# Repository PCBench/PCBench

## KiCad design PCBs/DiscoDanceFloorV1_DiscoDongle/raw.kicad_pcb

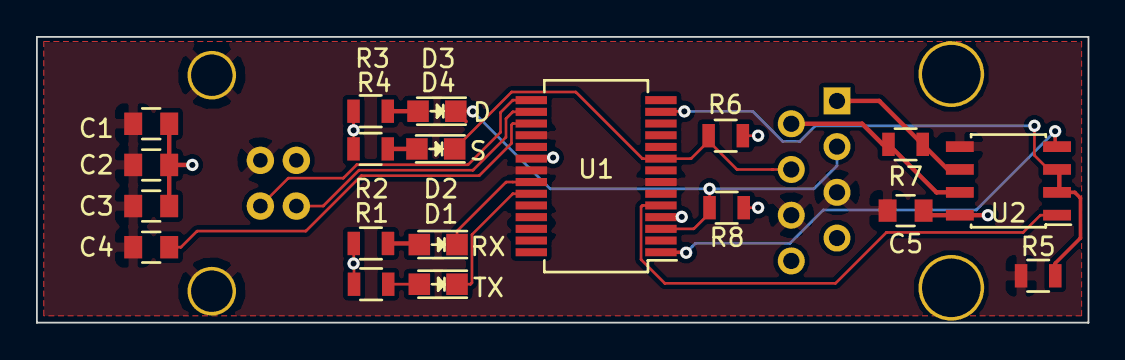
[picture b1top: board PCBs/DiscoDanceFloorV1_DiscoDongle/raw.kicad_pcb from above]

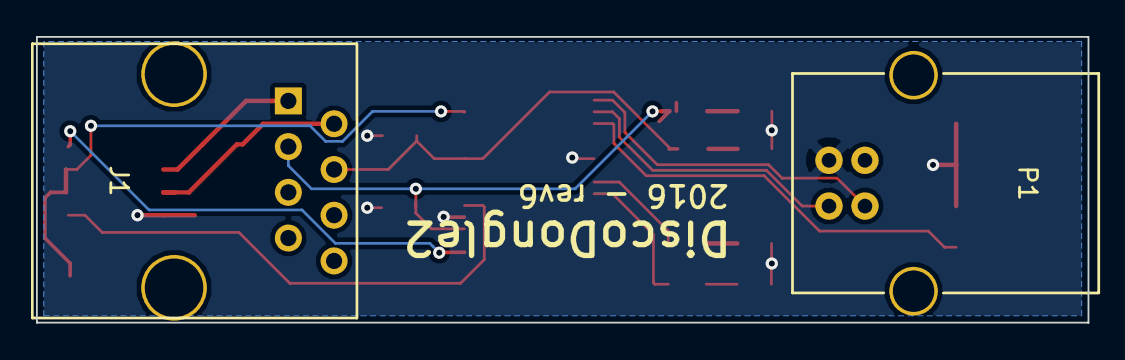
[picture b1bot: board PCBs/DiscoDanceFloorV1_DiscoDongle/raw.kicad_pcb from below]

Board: 2 copper layers, 58.4 x 15.9 mm, 21 parts (2 on the bottom side), 18 nets.

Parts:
C1, C4, C5: 100nF; C_0805
C2: 4.7uF; C_0805
C3: 10nF; C_0805
D1: TX; LED_0805
D2: RX; LED_0805
D3: D; LED_0805
D4: S; LED_0805
J1: RJ45; RJ45_8
P1: USB_B
R1, R2, R3, R4: 200; R_0805
R5, R6, R8: 20k; R_0805
R7: 120; R_0805
U1: FT232RL; SSOP-28_5.3x10.2mm_Pitch0.65mm
U2: ISL81487E; SOIC-8_3.9x4.9mm_Pitch1.27mm

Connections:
+5V: C1.1, C2.1, C3.1, C5.1, P1.1, R1.1, R2.1, R3.1, R4.1, R6.1, R8.1, U1.4, U1.20, U2.8
Daisy: D3.1, J1.3, R8.2, U1.3
GND: C1.2, C2.2, C3.2, C4.2, C5.2, J1.5, J1.6, P1.4, P1.5, R5.2, U1.7, U1.18, U1.21, U1.25, U1.26, U2.5
unnamed: C4.1, U1.17
unnamed: D1.2, R1.2
unnamed: D2.2, R2.2
unnamed: D3.2, R3.2
unnamed: D4.2, R4.2
unnamed: J1.1, R7.2, U2.6
unnamed: J1.2, R7.1, U2.7
unnamed: P1.2, U1.16
unnamed: P1.3, U1.15
unnamed: R5.1, U1.13, U2.2, U2.3
unnamed: U1.1, U2.4
unnamed: U1.5, U2.1
RXLED: D2.1, U1.22
Signal: D4.1, J1.4, R6.2, U1.9
TXLED: D1.1, U1.23

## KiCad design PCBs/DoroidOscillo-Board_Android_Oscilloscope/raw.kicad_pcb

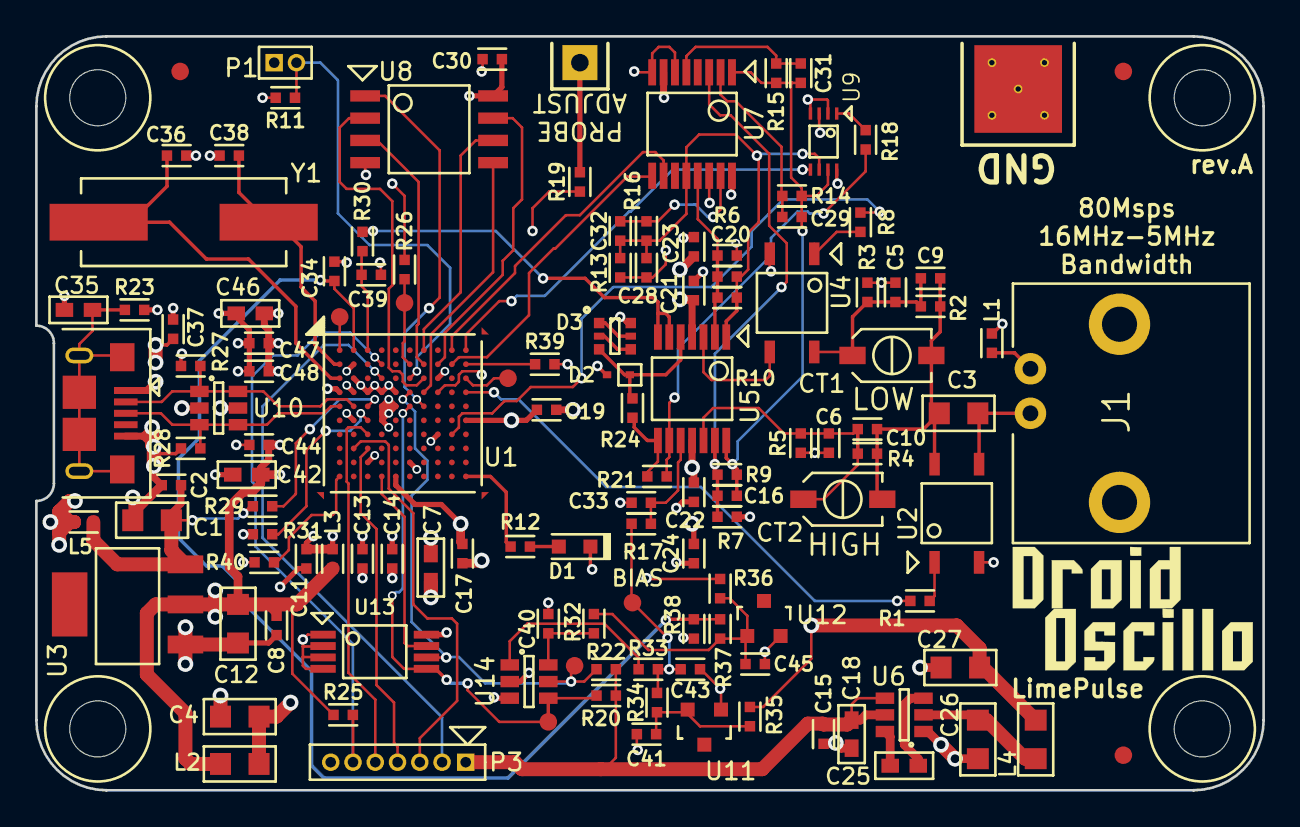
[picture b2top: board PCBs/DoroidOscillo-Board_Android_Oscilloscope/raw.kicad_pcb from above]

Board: 4 copper layers, 70.0 x 43.0 mm, 132 parts (0 on the bottom side), 77 nets.

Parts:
C1, C4, C12, C26, C27: 22u 6.3V; SMD2012
C2, C8, C11, C14, C15, C17, C19, C23, C24, C30, C33, C37, C41, C43, C44, C45, C47: 0.1u; SMD1005
C3: 47n 100V; SMD2012
C5, C32: 4.7p; SMD1005
C6: 120p; SMD1005
C7, C18, C42, C46: 10u 6.3V; SMD1608
C9, C10, C39: NM; SMD1005
C13, C48: 22n; SMD1005
C16, C20: 2.2p; SMD1005
C21, C22, C34, C40: 1u; SMD1005
C25: 4.7u 6.3V; SMD1608
C28: 15p; SMD1005
C29: 3.3p; SMD1005
C31: 10p; SMD1005
C35: 4.7n 100V; SMD1608
C36, C38: 18p; SMD1005
CT1: TZC3R100A110 3p-10p; MURATA_TZC3
CT2: TZC3Z030A110R00 1.4p-3p; MURATA_TZC3
D1: APT1608EC; SMD1608_DIODE
D2: RB521S30T5G; SOD-523
D3: BAS16VY; SOT-363
FID1: Fiducial_C; Fiducial_1mm
FID2: Fiducial_A; Fiducial_1mm
FID3: Fiducial_B; Fiducial_1mm
HOLE3MM_NC, HOLE3MM_NC#2, HOLE3MM_NC#3, HOLE3MM_NC#4: VAL**; HOLE3MM_NC
J1: BNC; BNC-R
L1, L5: BLM15AG121SN1; SMD1005
L2, L4: LBR2012T202K; SMD2012
L3: BLM15AG601SN1; SMD1005
P1: USB_BOOT; PIN_HEADER_2_1.27mm
P2: FCI_10118193-0001LF; 10118193-0001LF
P3: JTAG; PIN_HEADER_7_1.27pitch
R1, R8, R11, R36, R39, R40: 2.2k 5%; SMD1005
R2: 1100k 1%; SMD1005
R3: 910k 1%; SMD1005
R4: 1.96M 1%; SMD1005
R5: 36k 1%; SMD1005
R6, R7: 3k 1%; SMD1005
R9, R10: 27k 1%; SMD1005
R12: 10k 5%; SMD1005
R13: 3.3k 1%; SMD1005
R14: 22k 1%; SMD1005
R15: 5.6k 1%; SMD1005
R16: 13.3k 1%; SMD1005
R17, R32: 4.7k 5%; SMD1005
R18: 910 1%; SMD1005
R19, R29: 100 5%; SMD1005
R20, R22, R25, R26: 4.7k; SMD1005
R21: 1k 1%; SMD1005
R23, R27, R28: 1M 5%; SMD1005
R24: 680 1%; SMD1005
R30: 0; SMD1005
R31: 12k 1%; SMD1005
R33: 2k 1%; SMD1005
R34: 8.2k 1%; SMD1005
R35, R38: 1.5k 1%; SMD1005
R37: 2.2k 1%; SMD1005
TP1: SCL; TestPad
TP2: SDA; TestPad
TP3: RST; TestPad
U1: LPC4370FET100; TFBGA100_MYREFLOW
U2, U4: CPC1017N
U3: AMS1117-3.3; SOT-223
U5: OPA4354AIPWR; TSSOP-14_4.4x5mm_Pitch0.65mm
U6: LM2664; SOT-23-6
U7: 74HC4052PW; TSSOP-16_4.4x5mm_Pitch0.65mm
U8: W25Q80BVSSIG; SOIJ-8_5.3x5.3mm_Pitch1.27mm
U9: TC7W53FK; SSOP8_P0.5W2.3
U10: USBLC6-2SC6; SOT-23-6
U11, U12: LM385M3-1.2/NOPB; SOT-23
U13: AT24C02C-XHM-T; TSSOP-8_4.4x3mm_Pitch0.65mm
U14: MCP4726A0T-E/CH; SOT-23-6
W1: ISP; TestPad
W2: PROBE_COMP_HOLE
W3: ADC1; TestPad
W4: PROBE_GND_PAD; Probe-ADJ-GND
W5: TP_BIAS; TestPad
Y1: ABLS-12.000MHZ-B4-T; Crystal_HC49-SD_SMD

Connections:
/USB_D+: P2.3, R28.1, U1.E1, U10.3, U10.4
/USB_D-: P2.2, R27.1, U1.E2, U10.1, U10.6
/USB_VBUS: R29.1, U1.E3
ADCHS_VNEG: C39.1, R30.2, U1.A3
ADCHS_VPOS0: C34.1, R37.2, R38.1, U1.A2
BIAS: C43.2, R17.1, R33.2, R34.1, W5.1
BOOT1: R40.1, U1.K1
BOOT2: P1.2, R11.1, U1.C6
BOOT3: R39.1, U1.B10
BOOT_ISP: U1.C10, W1.1
DAC_OUT: R33.1, U14.1
DAC_VREF: C45.1, R32.1, R36.2, R37.1, U12.1
DC_SW: R1.1, U1.D10
EEPROM_WP: U1.K4, U13.7
GND: C1.2, C2.2, C4.2, C5.2, C6.2, C7.2, C8.2, C11.2, C12.2, C13.2, C14.2, C15.2, C17.2, C18.2, C19.2, C21.2, C22.1, C23.2, C24.1, C26.2, C27.2, C30.2, C33.2, C34.2, C35.2, C36.1, C37.2, C38.1, C39.2, C40.1, C41.2, C42.2, C43.1, C44.2, C45.2, C46.2, C47.2, C48.2, D1.1, D2.2, D3.6, L1.2, P2.5, P3.7, R3.1, R5.2, R6.2, R7.2, R11.2, R23.2, R27.2, R28.2, R31.2, R38.2, R39.2, R40.2, U1.C2, U1.C8, U1.D3, U1.D4, U1.D5, U1.F2, U1.G8, U1.J3, U1.J6, U2.2, U3.1, U4.2, U6.1, U7.6, U7.8, U8.4, U9.2, U9.4, U10.2, U11.1, U12.2, U13.1, U13.2, U13.3, U13.4, U14.2, W4.1
I2C_SCL: R22.2, TP1.1, U1.D6, U13.6, U14.5
I2C_SDA: R20.2, TP2.1, U1.E6, U13.5, U14.4
JTAG_RESET: P3.6, R25.2, U1.B4
JTAG_TCK: P3.3, U1.H2
JTAG_TDI: P3.5, U1.G3
JTAG_TDO: P3.4, U1.H3
JTAG_TMS: P3.2, U1.C4
LED0: R12.1, U1.K10
MUX0-S0: U1.A9, U7.10
MUX0-S1: U1.B9, U7.9
MUX1-A: U1.A10, U9.5
unnamed: C3.1, J1.C, U2.3
unnamed: C5.1, C9.2, CT1.2, R2.1, R3.2, U4.4
unnamed: C3.2, C9.1, C10.1, CT1.1, CT2.1, R2.2, R4.1, U2.4
unnamed: C6.1, C10.2, CT2.2, R4.2, R5.1, U5.12
unnamed: C7.1, C11.1, C13.1, C14.1, L3.2, U1.E4, U1.E5, U1.F4
unnamed: C16.1, C29.2, C31.2, R9.2, R14.2, R15.2, U5.14, U7.1, U9.7
unnamed: C16.2, R7.1, R9.1, U5.13, U7.3
unnamed: C20.1, R6.1, R10.2, U5.2, U7.13
unnamed: C20.2, C28.1, C32.1, R10.1, R13.1, R16.1, U5.1, U7.12, U9.6
unnamed: C25.1, U6.6
unnamed: C25.2, U6.3
unnamed: C26.1, L4.1, U6.2
unnamed: C28.2, R13.2, U7.14
unnamed: C29.1, R14.1, U7.2
unnamed: C31.1, R15.1, U7.5
unnamed: C32.2, R16.2, U7.15
unnamed: C33.1, R17.2, U5.10
unnamed: C35.1, P2.S1, P2.S2, P2.S3, P2.S4, P2.S5, P2.S6, R23.1
unnamed: C36.2, U1.C1, Y1.1
unnamed: C37.1, L5.1, P2.1, U10.5
unnamed: C38.2, U1.B1, Y1.2
unnamed: C40.2, R32.2, U14.6
unnamed: C41.1, R34.2, R35.1, U11.2
unnamed: D1.2, R12.2
unnamed: D2.1, D3.3, R24.2, U5.5
unnamed: D3.1, D3.5
unnamed: D3.2, D3.4
unnamed: J1.S, L1.1
unnamed: R1.2, U2.1
unnamed: R8.1, U4.1
unnamed: R18.1, R21.2, U5.9
unnamed: R18.2, U9.1
unnamed: R19.1, W2.1
unnamed: R21.1, R24.1, U5.8
unnamed: R26.2, TP3.1, U1.B6
unnamed: R30.1, U5.6, U5.7
unnamed: R31.1, U1.F3
unnamed: U1.A1, W3.1
unnamed: U4.3, U5.3
OP_SW: R8.2, U1.G9
PROBE_COMP: R19.2, U1.D8
SPIFI_CS: U1.E7, U8.1
SPIFI_MISO: U1.C7, U8.2
SPIFI_MOSI: U1.D7, U8.5
SPIFI_SCK: U1.A7, U8.6
SPIFI_SIO2: U1.B7, U8.3
SPIFI_SIO3: U1.B8, U8.7
VBUS: C1.1, C2.1, L5.2, R29.2, U3.3
alt_3.3VD: C8.1, C12.1, C15.1, C17.1, C18.1, C19.1, C30.1, C42.1, C44.1, C46.1, C47.1, C48.1, L2.1, L3.1, P1.1, P3.1, R20.1, R22.1, R25.1, R26.1, U1.B2, U1.D1, U1.D2, U1.F10, U1.K5, U3.2, U6.4, U6.5, U8.8, U13.8
alt_VAA+: C4.1, C21.1, C23.1, L2.2, R36.1, U5.4, U7.16, U9.8, U14.3
alt_VAA-: C22.2, C24.2, C27.1, L4.2, R35.2, U5.11, U7.7, U9.3

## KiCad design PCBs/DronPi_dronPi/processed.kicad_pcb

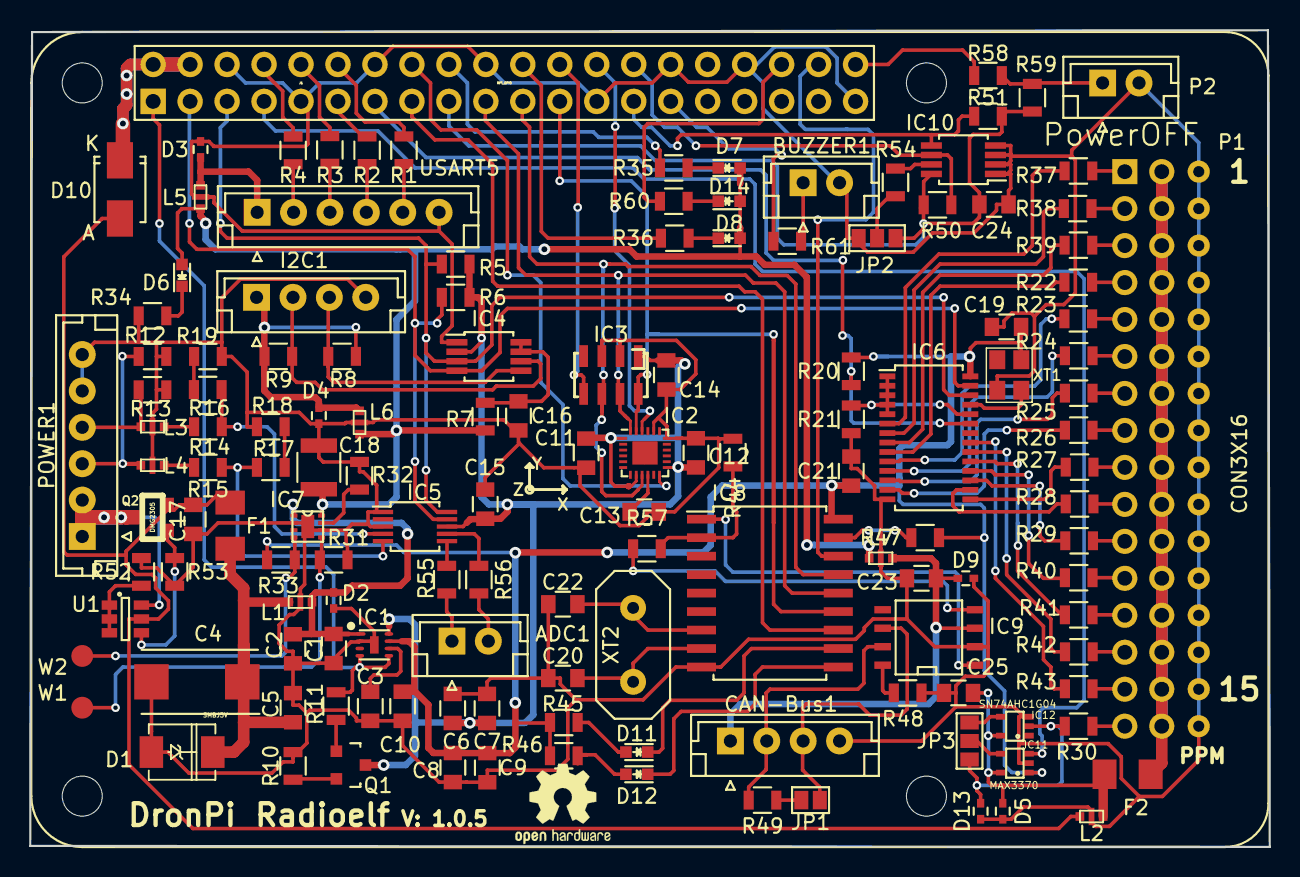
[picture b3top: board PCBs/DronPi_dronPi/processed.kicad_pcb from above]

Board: 2 copper layers, 85.2 x 56.1 mm, 141 parts (0 on the bottom side), 125 nets.

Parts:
ADC1: CONN_01X02; JST_EH_B02B-EH-A_02x2.50mm_Straight
BUZZER1: CONN_01X04; JST_EH_B02B-EH-A_02x2.50mm_Straight
C1, C5, C7, C10, C11, C14, C15, C16, C19, C21, C23, C24, C25: 100nF; C_0805
C2: 10uF; C_0805
C3: 2u2F; C_0805
C4: 220uF; TantalC_SizeD_EIA-7343_Reflow
C6, C9, C17: 22uF; C_0805
C8: 1uF; C_0805
C12: 10nF; C_0805
C13: 2u2; C_0805
C18: 100uF; C_1210
C20, C22: 22pF; C_0805
CAN-Bus1: JST_4PIN; JST_EH_B04B-EH-A_04x2.50mm_Straight
D1: SMBJ5V; DO-214AA
D2, D3, D4, D5, D9, D13: PESD0402-140; C_0402
D6: LED_rojo; LED_0603
D7: LED_verde; LED_0603
D8: LED_azul; LED_0603
D10: STPS1L30A; SMA_Standard
D11: verde; LED_0603
D12: Rojo; LED_0603
D14: LED_blanco; LED_0603
F1, F2: 0ZCA0035FF2G; Fuse_SMD1206_Wave
I2C1: JST_4PIN; JST_EH_B04B-EH-A_04x2.50mm_Straight
IC1: MIC5332; MLF-8-1EP
IC2: MPU-9250; QFN-24-1EP_3x3mm_Pitch0.4mm
IC3: MS5611-01BA; MS5611
IC4: PCA9306; MSOP-8_3x3mm_Pitch0.65mm
IC5: ADC_ADS1115; MSOP-10_3x3mm_Pitch0.5mm
IC6: PCA9685; TSSOP-28_4.4x9.7mm_Pitch0.65mm
IC7: BQ24315; BQ24313_DSG_8
IC8: MCP2515; SOIC-18
IC9: MCP2551; SOIC-8-N
IC10: 24AA32; MSOP-8_3x3mm_Pitch0.65mm
IC11: MAX3370; SC70-5
IC12: SN74AHC1G04; SC70-5
J1: RPi_GPIO; raspberrypi2
JP1: JUMPER; GS2
JP2, JP3: JUMPER3; GS3
L1, L2, L3, L4, L5, L6, L7: KNH16C104DA5TS; KYOCERA-KNH16-DA
M1: OSHW-LOGOS; OSHW-Logo2_7.3x6mm_SilkScreen
P1: CONN_3X16; IDC_Header_Straight_34pins
P2: PowerOff; JST_EH_B02B-EH-A_02x2.50mm_Straight
POWER1: JST_6PIN; JST_EH_B06B-EH-A_06x2.50mm_Straight
Q1: MMBT3906LT1; SOT-23
Q2: DMG2305; SOT23-3
R1, R2, R3, R4, R49: 120R; R_0805
R5, R6, R8, R9: 1K5; R_0805
R7: 200K; R_0805
R10: 10R; R_0805
R11: 1k8; R_0805
R12, R13, R33: 1M; R_0805
R14, R15, R16, R17, R18, R19, R55, R56: 10K/0.1%; R_0805
R20, R21, R31, R47: 10K; R_0805
R22, R23, R24, R25, R26, R27, R28, R29, R37, R38, R39, R40, R41, R42, R43: 220; R_0805
R30: 100; R_0805
R32: 24K; R_0805
R34, R35, R60: 680; R_0805
R36: 820; R_0805
R44: 18K; R_0805
R45, R46: 560; R_0805
R48, R54: 1K; R_0805
R50: 3K9; R_0805
R51: 3k9; R_0805
R52: 47k; R_0805
R53: 47K; R_0805
R57, R59: 10k; R_0805
R58: 1k; R_0805
R61: 100R; R_0805
U1: DMMT5401; SOT-23-6
USART5: JST_6PIN; JST_EH_B06B-EH-A_06x2.50mm_Straight
W1: REG_CE; Measurement_Point_Round-SMD-Pad_Small
W2: REG_FAULT; Measurement_Point_Round-SMD-Pad_Small
XT1: CRYSTAL_ASE-25mhz; ASEseries
XT2: 16Mhz; HC-18UV

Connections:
3v3: C24.2, IC10.8, J1.17, JP2.1, R50.1, R51.1, R59.1
3v3_EN: IC1.4, IC1.5, J1.1, R11.1
+3v3: C6.1, C7.1, C11.1, C12.1, C14.1, C15.1, IC1.8, IC2.1, IC2.8, IC2.13, IC3.1, IC4.2, IC5.8, Q1.3, R5.1, R6.1
+5v_SERV: C25.2, D5.1, F2.2, IC11.5, IC12.5, L2.P$2
/I2C/SCL2: I2C1.2, IC4.6, R9.2
/I2C/SDA2: I2C1.3, IC4.5, R8.2
/PWM-PPM-SBUS/PPM_: D13.1, IC12.2, JP3.1, R30.2
/PWM-PPM-SBUS/SBUS_: IC12.4, JP3.3
/Proteccion/REG_CE: IC7.5, R31.2, W1.1
/Proteccion/REG_FAULT: IC7.4, R33.1, W2.1
ANL_I: L4.P$1, POWER1.3, R12.1
ANL_V: L3.P$1, POWER1.4, R13.1
BBB_+3v3: C8.1, C9.1, C10.1, C19.1, C21.2, IC1.7, IC6.28, IC8.18, IC11.1, R20.1, R33.2, R45.1, R46.1, R47.2, XT1.4
BUZZER: J1.29, R61.2
GND: BUZZER1.2, C1.2, C2.2, C3.2, C4.2, C5.2, C6.2, C7.2, C8.2, C9.2, C10.2, C11.2, C12.2, C13.2, C14.2, C15.2, C16.2, C17.2, C18.2, C19.2, C20.2, C21.1, C22.2, C23.2, C24.1, C25.1, CAN-Bus1.4, D1.1, D2.2, D3.2, D4.2, D5.2, D9.2, D13.2, I2C1.4, IC1.2, IC1.9, IC2.18, IC2.20, IC3.2, IC3.3, IC4.1, IC5.1, IC5.3, IC6.14, IC7.2, IC7.6, IC7.9, IC8.9, IC9.2, IC10.1, IC10.2, IC10.3, IC10.4, IC11.2, IC12.3, J1.6, J1.9, J1.14, J1.20, J1.25, J1.30, J1.34, J1.39, JP2.3, L1.P$3, L1.P$4, L1.P$5, L2.P$3, L2.P$4, L2.P$5, L3.P$3, L3.P$4, L3.P$5, L4.P$3, L4.P$4, L4.P$5, L5.P$3, L5.P$4, L5.P$5, L6.P$3, L6.P$4, L6.P$5, L7.P$3, L7.P$4, L7.P$5, P1.3, P1.6, P1.9, P1.12, P1.15, P1.18, P1.21, P1.24, P1.27, P1.30, P1.33, P1.36, P1.39, P1.42, P1.45, P1.48, P2.2, POWER1.5, POWER1.6, R10.2, R12.2, R13.2, R18.2, R19.2, R21.2, R31.1, R32.1, R34.2, R44.1, R48.2, R52.2, R53.2, USART5.6, XT1.2
HAT_SCL: IC10.6, J1.28, R50.2
HAT_SDA: IC10.5, J1.27, R51.2
INT_CAN: IC8.12, J1.15
LED_1: J1.18, R35.2
LED_2: J1.22, R36.2
LED_3: J1.36, R60.2
MPU_INT: IC2.12, J1.16
unnamed: ADC1.1, R55.2
unnamed: ADC1.2, R56.2
unnamed: BUZZER1.1, R61.1
unnamed: C3.1, IC1.6
unnamed: C4.1, C5.1, D1.2, F1.2, L1.P$1
unnamed: C13.1, IC2.10
unnamed: C16.1, IC4.7, IC4.8, R7.2
unnamed: C20.1, IC8.8, XT2.1
unnamed: C22.1, IC8.7, XT2.2
unnamed: C23.1, CAN-Bus1.1, D9.1, IC9.3, L7.P$2
unnamed: CAN-Bus1.2, IC9.7, R49.2
unnamed: CAN-Bus1.3, IC9.6, JP1.2
unnamed: D3.1, L5.P$1, USART5.1
unnamed: D4.1, I2C1.1, L6.P$2, R8.1, R9.1
unnamed: D6.1, R34.1
unnamed: D7.1, R35.1
unnamed: D8.1, R36.1
unnamed: D11.1, IC8.11
unnamed: D11.2, R45.2
unnamed: D12.1, IC8.10
unnamed: D12.2, R46.2
unnamed: D14.1, R60.1
unnamed: F2.1, P1.2, P1.5, P1.8, P1.11, P1.14, P1.17, P1.20, P1.23, P1.26, P1.29, P1.32, P1.35, P1.38, P1.41, P1.44, P1.47
unnamed: IC5.4, R14.2, R16.2
unnamed: IC5.5, R15.1, R17.2
unnamed: IC5.6, R55.1
unnamed: IC5.7, R56.1
unnamed: IC6.1, IC6.2, IC6.3, IC6.4, IC6.5, IC6.24, R21.1
unnamed: IC6.6, R37.2
unnamed: IC6.7, R38.2
unnamed: IC6.8, R39.2
unnamed: IC6.9, R22.2
unnamed: IC6.10, R23.2
unnamed: IC6.11, R24.2
unnamed: IC6.12, R25.2
unnamed: IC6.13, R26.2
unnamed: IC6.15, R27.2
unnamed: IC6.16, R28.2
unnamed: IC6.17, R29.2
unnamed: IC6.18, R40.2
unnamed: IC6.19, R41.2
unnamed: IC6.20, R42.2
unnamed: IC6.21, R43.2
unnamed: IC6.25, XT1.3
unnamed: IC7.7, R32.2
unnamed: IC8.1, IC9.1
unnamed: IC8.2, R44.2, R57.2
unnamed: IC8.17, R47.1
unnamed: IC9.4, R57.1
unnamed: IC9.8, R48.1
unnamed: IC10.7, R54.2
unnamed: IC11.4, JP3.2
unnamed: JP1.1, R49.1
unnamed: JP2.2, R54.1
unnamed: L3.P$2, R14.1
unnamed: L4.P$2, R15.2
unnamed: P1.1, R37.1
unnamed: P1.4, R38.1
unnamed: P1.7, R39.1
unnamed: P1.10, R22.1
unnamed: P1.13, R23.1
unnamed: P1.16, R24.1
unnamed: P1.19, R25.1
unnamed: P1.22, R26.1
unnamed: P1.25, R27.1
unnamed: P1.28, R28.1
unnamed: P1.31, R29.1
unnamed: P1.34, R40.1
unnamed: P1.37, R41.1
unnamed: P1.40, R42.1
unnamed: P1.43, R43.1
unnamed: P1.46, R30.1
unnamed: P2.1, R58.1, R59.2
unnamed: POWER1.1, POWER1.2, Q2.3, U1.6
unnamed: Q1.1, R11.2
unnamed: Q1.2, R10.1
unnamed: Q2.1, R53.1, U1.4
unnamed: R1.2, USART5.5
unnamed: R2.2, USART5.4
unnamed: R3.2, USART5.3
unnamed: R4.2, USART5.2
unnamed: R16.1, R19.1
unnamed: R17.1, R18.1
unnamed: R52.1, U1.1, U1.2, U1.3
PPM: IC11.3, J1.7
PWM_EN: IC6.23, J1.13, R20.2
Power: C17.1, D10.2, F1.1, L2.P$1, Q2.2, U1.5
PowerOff: J1.40, R58.2
SCL: IC4.3, IC5.10, IC6.26, J1.5, R5.2
SDA: IC4.4, IC5.9, IC6.27, J1.3, R6.2
SPI_CLK: IC2.23, IC3.8, IC8.13, J1.23
SPI_CS_BARO: IC3.5, J1.24
SPI_CS_CAN: IC8.16, J1.38
SPI_CS_MPU: IC2.22, J1.26
SPI_MISO: IC2.9, IC3.6, IC8.15, J1.21
SPI_MOSI: IC2.24, IC3.7, IC8.14, J1.19
UART_CTS: J1.11, R2.1
UART_RTS: J1.12, R1.1
UART_RX: J1.10, R3.1
UART_TX: J1.8, R4.1
VCC_AUX: C18.1, D6.2, D7.2, D8.2, D14.2, IC7.8, L5.P$2, L6.P$1, L7.P$1, R7.1
VDD: D10.1, J1.2, J1.4
VDD_5v: C1.1, C2.1, D2.1, IC1.1, IC7.1, L1.P$2

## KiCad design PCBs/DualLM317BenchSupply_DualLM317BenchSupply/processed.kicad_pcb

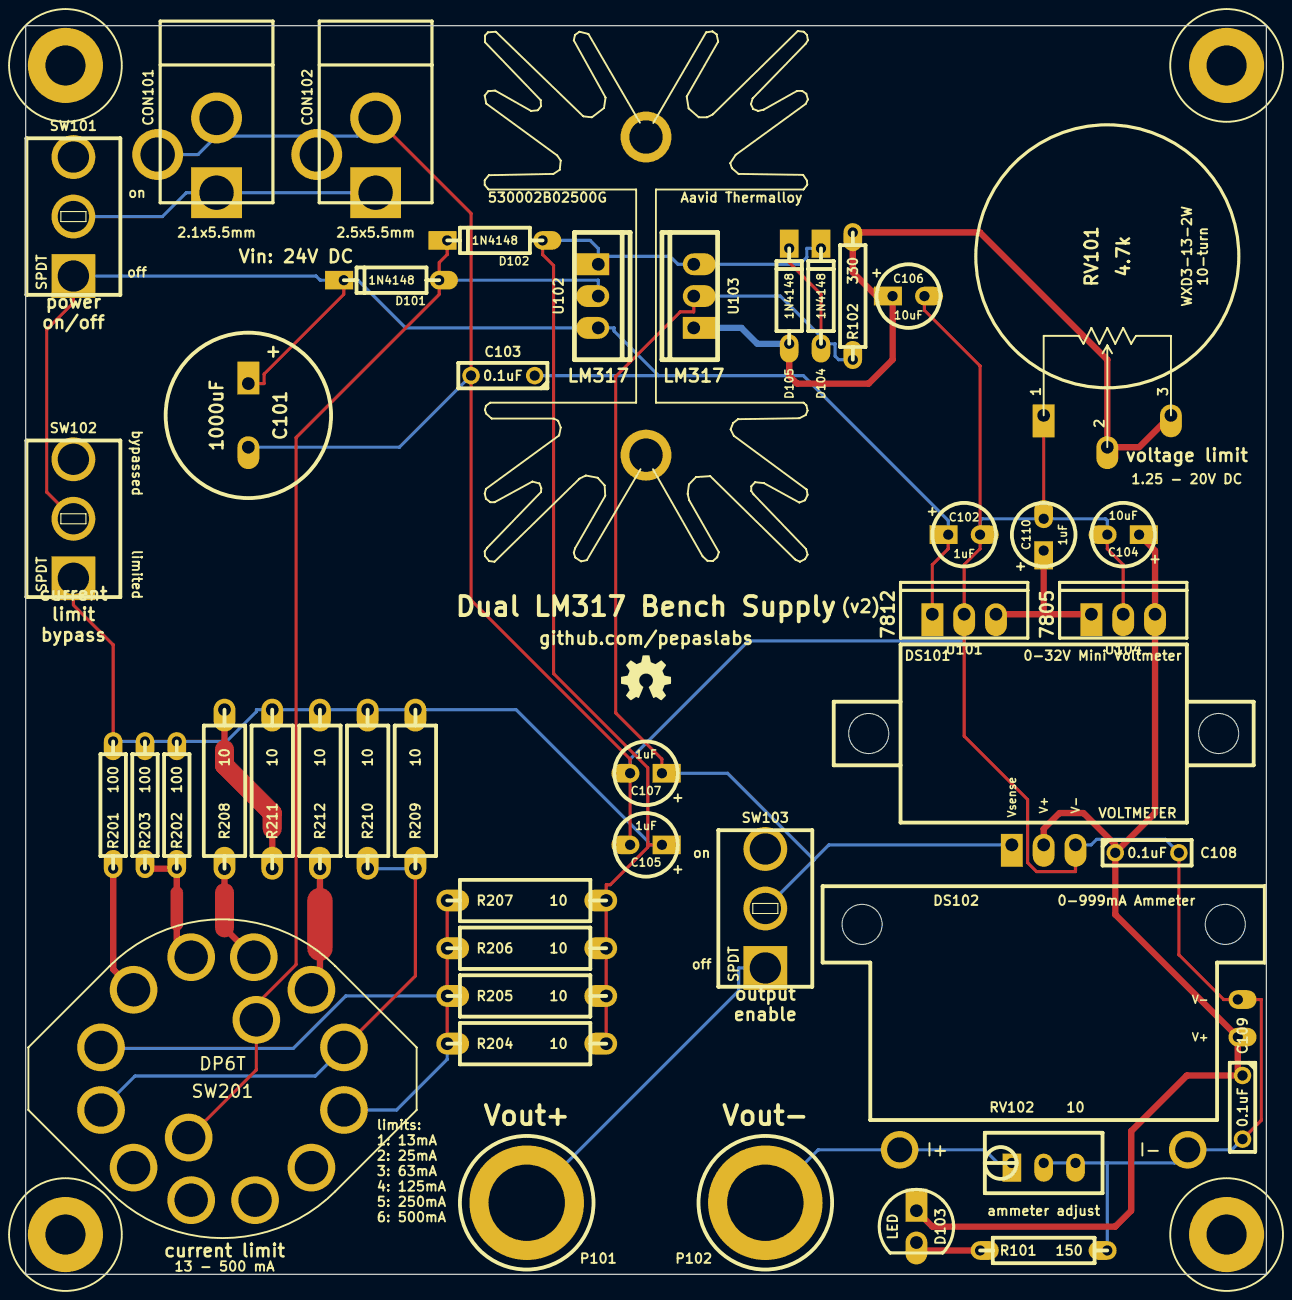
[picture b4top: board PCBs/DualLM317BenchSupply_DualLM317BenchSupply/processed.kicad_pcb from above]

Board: 2 copper layers, 99.1 x 99.7 mm, 50 parts (0 on the bottom side), 19 nets.

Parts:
C101: 1000uF; ELCAP_20_52_V
C102, C105, C107, C110: 1uF; ELCAP_10_20_V
C103, C108, C109: 0.1uF; C2
C104, C106: 10uF; ELCAP_10_20_V
CON101: BARREL_JACK; BARREL_JACK_21x55
CON102: BARREL_JACK; BARREL_JACK_25x55
D101, D102, D104, D105: 1N4148; DIODE_3
D103: LED; LED_5MM
DS101: VOLTMETER; DVM036A
DS102: AMMETER_V; EBAY_AMMETER
H101, H102, H103, H104: HOLE; hole_M3
H***: 530002B02500G
P101: Vout+; Banana_A
P102: Vout-; Banana_A
R101: 150; R_AXIAL_0W25
R102: 330; R_AXIAL_0W25
R201, R202, R203: 100; R_AXIAL_0W25
R204, R205, R206, R207, R208, R209, R210, R211, R212: 10; R_AXIAL_0W5
RV101: 4.7k; WXD3-13-2W_A
RV102: 10; 3296W
SW101, SW102, SW103: SPDT; M2012SS1W01
SW201: DP6T; G3SR022-R
U101: 7812; TO-220_V_069B
U102, U103: LM317; TO-220_V_069B
U104: 7805; TO-220_V_069B

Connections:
5V: C104.1, C108.1, C109.1, D103.1, DS101.2, DS102.3, U104.3
12V: C110.1, U101.3, U104.1
/current_limit_r/R_LIM+: D101.1, D102.2, SW201.1, SW201.8, U102.2
/current_limit_r/R_LIM-: C105.1, D102.1, D104.2, R201.2, R202.2, R203.2, R204.2, R205.2, R206.2, R207.2, R209.2, R210.2, R211.2, R212.2, SW102.1, U102.1, U103.3
GND: C101.2, C102.2, C103.2, C104.2, C105.2, C106.2, C107.2, C108.2, C109.2, C110.2, CON101.2, CON101.3, CON102.2, CON102.3, DS101.3, DS102.2, DS102.4, R101.2, RV101.1, RV102.2, RV102.3, U101.2, U104.2
unnamed: C107.1, D104.1, D105.2, DS101.1, R102.1, SW103.2, U103.2
unnamed: C106.1, D105.1, R102.2, RV101.2, RV101.3, U103.1
unnamed: P101.1, SW103.1
unnamed: DS102.1, P102.1, RV102.1
unnamed: D103.2, R101.1
unnamed: CON101.1, CON102.1, SW101.2
unnamed: C101.1, C102.1, C103.1, D101.2, SW101.1, SW102.2, U101.1, U102.3
unnamed: R209.1, R210.1, SW201.6, SW201.13
unnamed: R204.1, R205.1, R206.1, R207.1, SW201.7, SW201.14
unnamed: R208.2, R211.1
unnamed: R212.1, SW201.5
unnamed: R208.1, SW201.4
unnamed: R201.1, SW201.2
unnamed: R202.1, R203.1, SW201.3

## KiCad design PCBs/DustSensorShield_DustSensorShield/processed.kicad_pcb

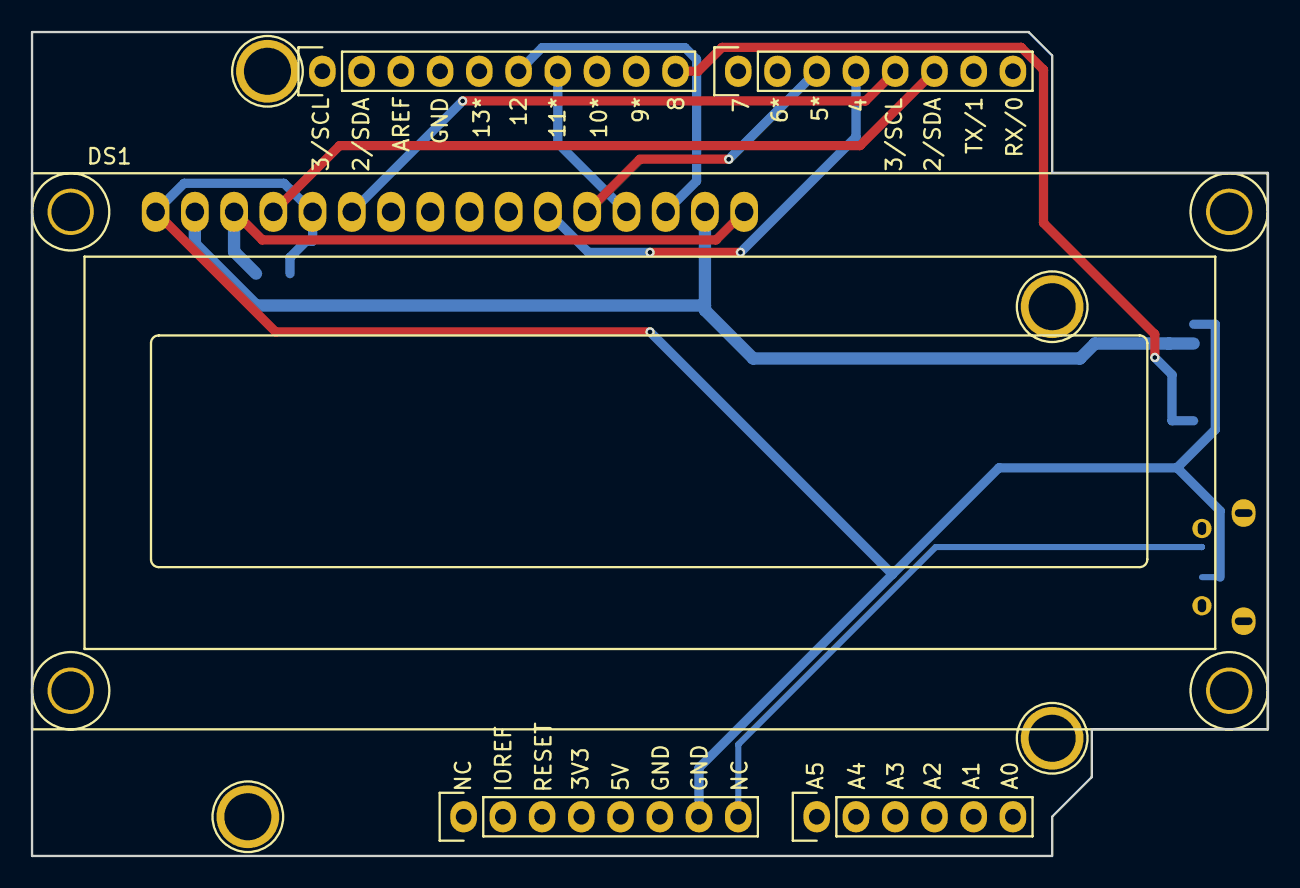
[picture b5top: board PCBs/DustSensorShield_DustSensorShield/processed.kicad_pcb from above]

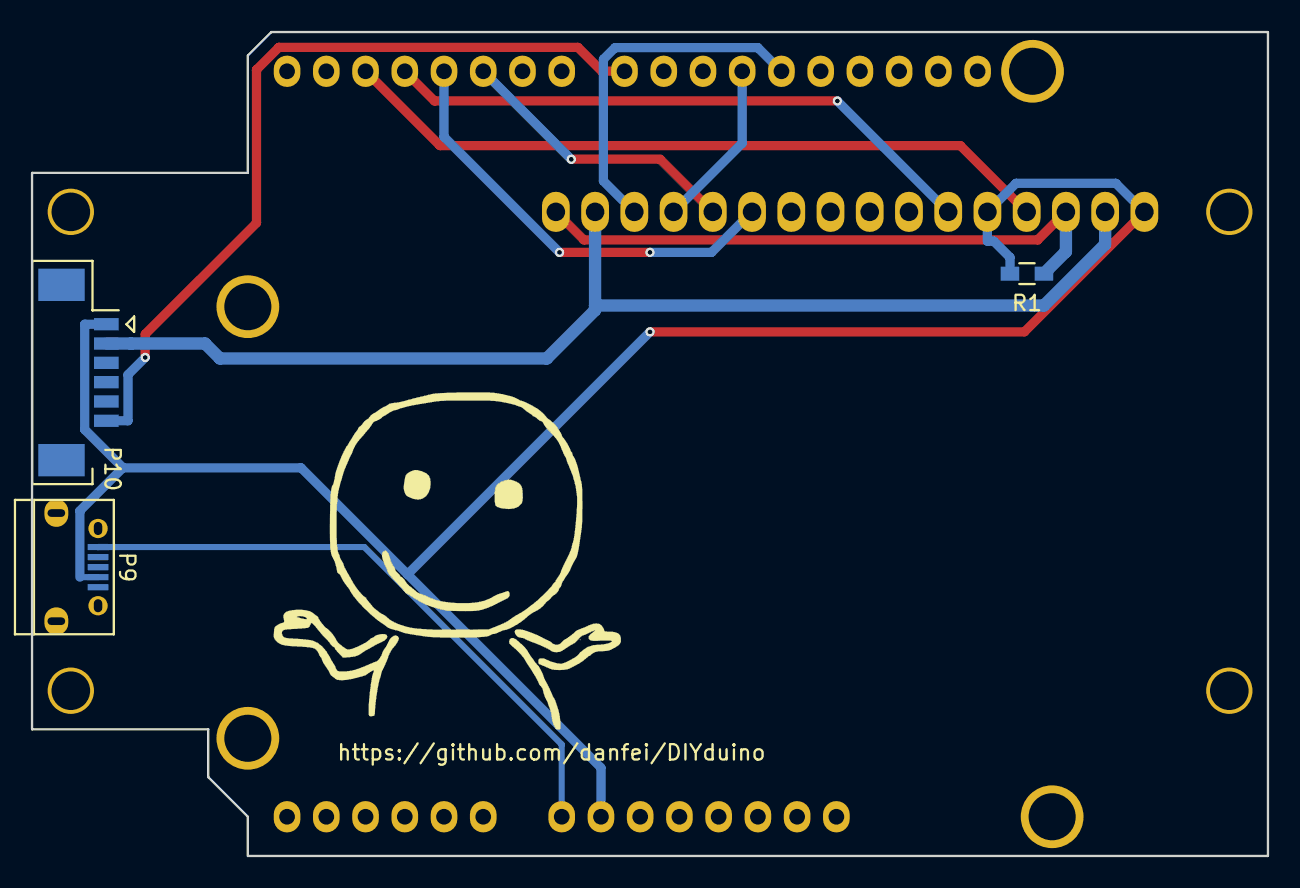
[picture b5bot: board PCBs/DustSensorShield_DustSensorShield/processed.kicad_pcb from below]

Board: 2 copper layers, 80.0 x 53.3 mm, 12 parts (3 on the bottom side), 11 nets.

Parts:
DS1: LCD16X2; WC1602A
P1: Power; Socket_Strip_Arduino_1x08
P2: Analog; Socket_Strip_Arduino_1x06
P3: Digital; Socket_Strip_Arduino_1x10
P4: Digital; Socket_Strip_Arduino_1x08
P5, P6, P7, P8: CONN_1; Arduino_1pin
P9: USB_B; USB_Micro-B
P10: CONN_01X06; Molex_PicoBlade_53261-0671
R1: 91R; R_0603_HandSoldering

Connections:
+5V: DS1.2, DS1.15, P10.2
/IO2: DS1.4, P4.6
/IO3: DS1.6, P4.5
/IO4: DS1.11, P4.4
/IO5: DS1.12, P4.3
/IO8: P3.10, P10.6
/IO11: DS1.13, P3.7
/IO12: DS1.14, P3.6
/VIN: P1.8, P9.1
GND: DS1.1, DS1.5, P1.7, P9.4, P10.1, R1.2
unnamed: DS1.3, DS1.16, R1.1

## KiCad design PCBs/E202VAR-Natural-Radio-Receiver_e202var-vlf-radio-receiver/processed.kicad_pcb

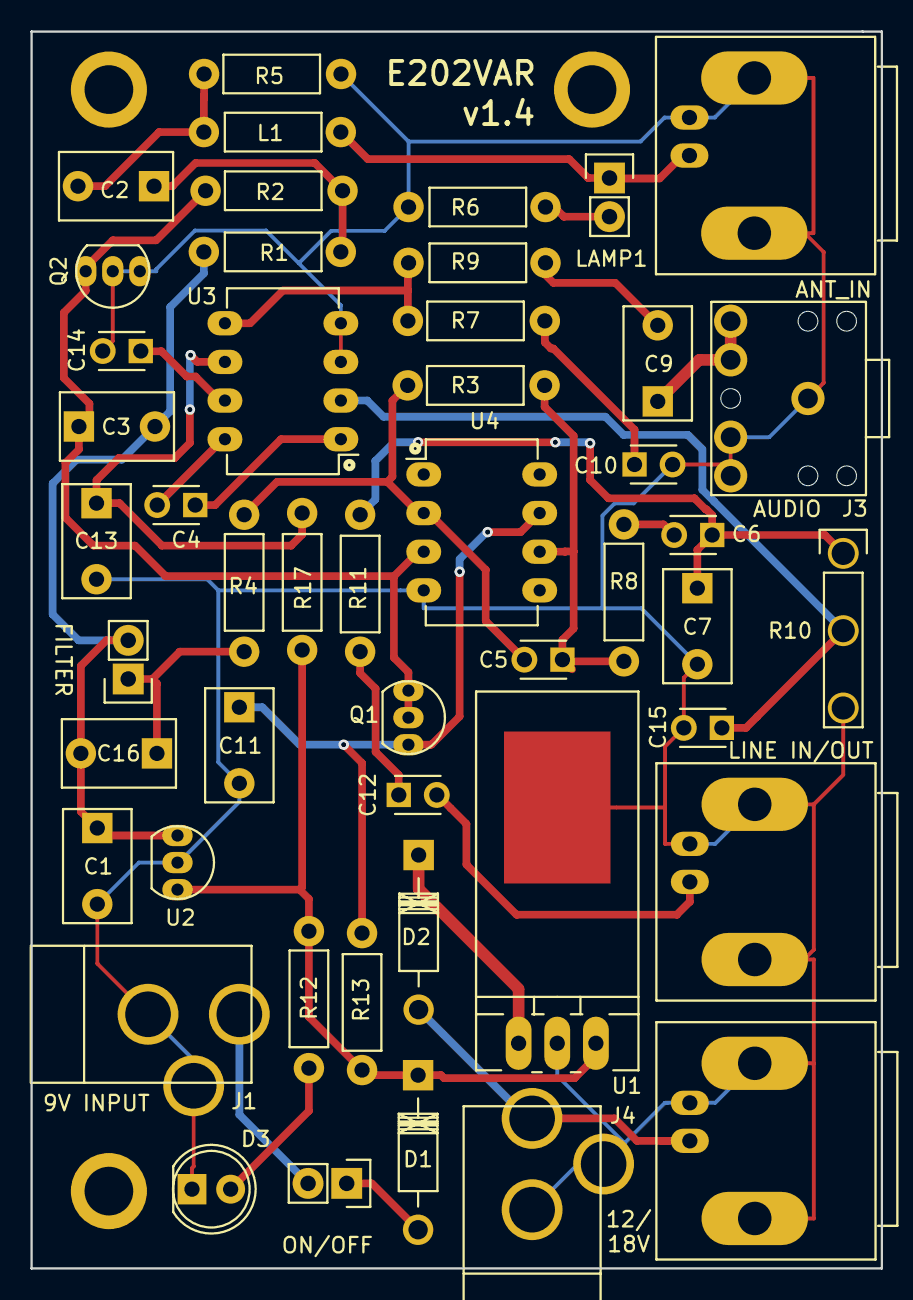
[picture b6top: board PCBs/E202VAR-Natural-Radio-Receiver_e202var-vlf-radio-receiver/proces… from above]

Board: 2 copper layers, 55.9 x 81.3 mm, 51 parts (0 on the bottom side), 30 nets.

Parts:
BNC1: 12/18V; CONN-BNC-TECONN-1-1634612-0
BNC2: ANT IN; CONN-BNC-TECONN-1-1634612-0
BNC3: LINE IN/OUT; CONN-BNC-TECONN-1-1634612-0
C1: 33nF; CAP-DISC-D7.5MM-P5MM
C2, C11: 100nF; CAP-DISC-D7.5MM-P5MM
C3: 8.2pF; CAP-DISC-D7.5MM-P5MM
C4, C6, C12: 10uF; CAP-DISC-D3MM-P2.5MM
C5: 150pF; CAP-DISC-D3MM-P2.5MM
C7, C16: 4.7nF; CAP-DISC-D7.5MM-P5MM
C9, C13: 100uF; CAP-DISC-D7.5MM-P5MM
C10: 10nF; CAP-DISC-D3MM-P2.5MM
C14, C15: 22nF; CAP-DISC-D3MM-P2.5MM
D1, D2: 1N4001; DIODE-DO-41
D3: BLUE; LED-D5MM-2PIN
H1, H2, H3: HOLE-PLATED-3.2MM
J1: 9V; CONN-BARREL-JACK-2.5x5.5MM-TH
J2: ON/OFF; CONN-ONSHORE-SCREW-GREEN-2PIN-TH
J3: HEADPHONES; SJ1-3523N
J4: 12V/18V; CONN-BARREL-JACK-2.5x5.5MM-TH
J5: FILTER; CONN-ONSHORE-SCREW-GREEN-2PIN-TH
L1: 3.3UH; RES-CARBONFILM-7MM
LAMP1: NEON; CONN-HEADER-STRAIGHT-P2.54MM-1x02
Q1, Q2: BC547; TO-92-INLINE-NARROW-OVAL
R1, R5: 10M; RES-CARBONFILM-7MM
R2, R3, R6: 100K; RES-CARBONFILM-7MM
R4: 3.3k; RES-CARBONFILM-7MM
R7: 10; RES-CARBONFILM-7MM
R8: 10K; RES-CARBONFILM-7MM
R9, R17: 33; RES-CARBONFILM-7MM
R10: 10K; RES-TRIMPOT-TTELEC-P160-TH
R11: 4.7K; RES-CARBONFILM-7MM
R12: 2.2K; RES-CARBONFILM-7MM
R13: 1K; RES-CARBONFILM-7MM
U1: MC7809; TO-220-NEUTRAL123-HORZ-LONGPADS
U2: TLE2426; TO-92-INLINE-NARROW-OVAL
U3: NJM386; DIP-8-W7.62MM-LONGPADS
U4: TL081CP; DIP-8-W7.62MM-LONGPADS

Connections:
+2V: C1.1, C3.2, C16.2, J5.2, R1.2, U2.1
+9V: D1.1, R12.1, R13.1, R17.1, U1.3, U2.3
GND: BNC1.2, BNC2.2, BNC3.2, C1.2, C7.2, C10.2, C11.2, C13.2, C14.2, C15.2, D3.1, J1.2, J1.3, J3.3, J3.4, J3.5, J4.2, J4.3, Q2.1, Q2.2, R5.2, R6.2, R10.3, U1.2, U2.2, U3.3, U3.4, U4.4
unnamed: BNC1.1, D2.2, J4.1
unnamed: BNC2.1, L1.1, LAMP1.1
unnamed: BNC3.1, C12.2
unnamed: C2.1, R1.1, R2.2
unnamed: C2.2, L1.2, R5.1
unnamed: C3.1, Q1.1, Q1.2, Q2.3, R2.1, U4.3
unnamed: C4.1, U3.1
unnamed: C4.2, U3.8
unnamed: C5.1, R3.2, R8.2, U4.6
unnamed: C5.2, R3.1, R4.1, U4.2
unnamed: C6.1, C7.1, R10.1, R11.2
unnamed: C6.2, R8.1
unnamed: C9.1, J3.1, J3.2
unnamed: C9.2, R9.1
unnamed: C10.1, R7.2
unnamed: C11.1, Q1.3, R13.2, U4.7
unnamed: C12.1, R11.1
unnamed: C13.1, R17.2, U3.6
unnamed: C14.1, U3.7
unnamed: C15.1, R10.2, U3.2
unnamed: C16.1, J5.1, R4.2
unnamed: D1.2, J2.1
unnamed: D2.1, U1.1
unnamed: D3.2, R12.2
unnamed: J1.1, J2.2
unnamed: LAMP1.2, R6.1
unnamed: R7.1, R9.2, U3.5

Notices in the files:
PCBs/E202VAR-Natural-Radio-Receiver_e202var-vlf-radio-receiver/processed.kicad_pcb:
CERN Open Hardware License v1.2
parts and their libraries:
Copyright 2016 Accelerated Designs. All rights reserved.
